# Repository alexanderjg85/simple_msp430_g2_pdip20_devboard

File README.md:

# simple_msp430_g2_pdip20_devboard

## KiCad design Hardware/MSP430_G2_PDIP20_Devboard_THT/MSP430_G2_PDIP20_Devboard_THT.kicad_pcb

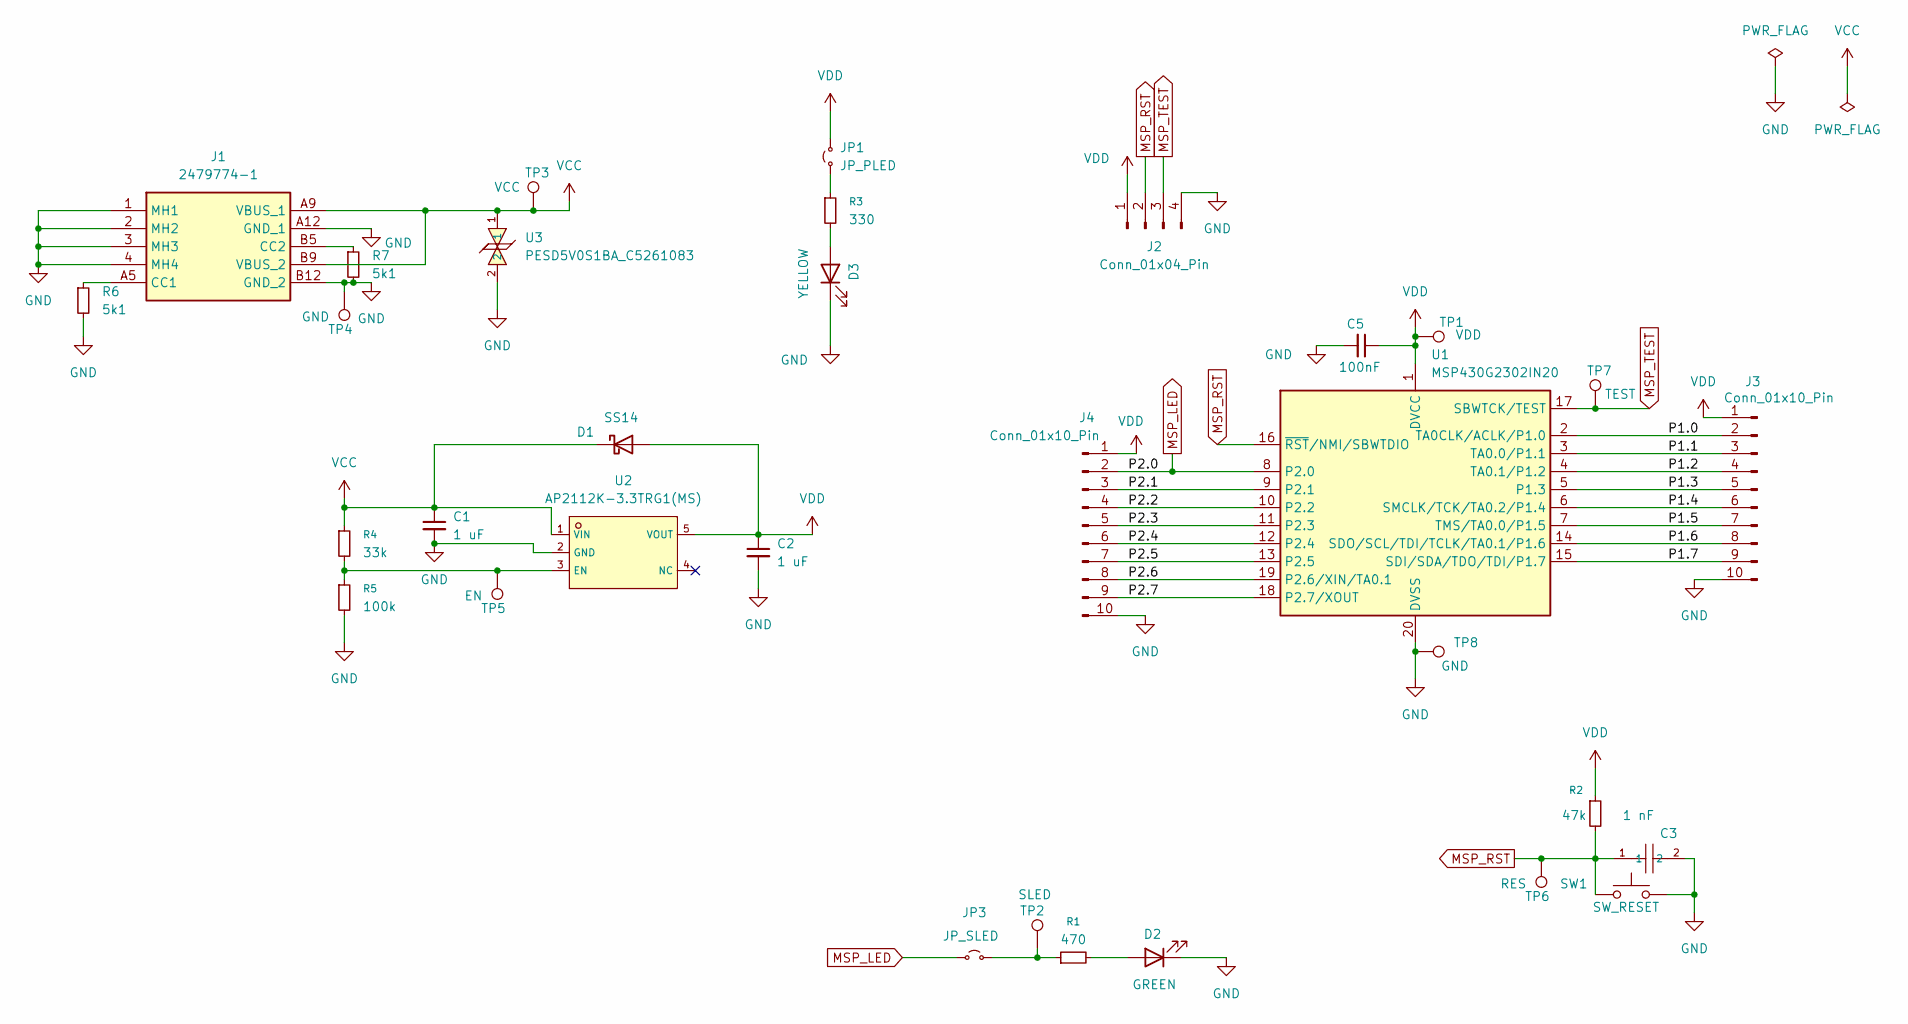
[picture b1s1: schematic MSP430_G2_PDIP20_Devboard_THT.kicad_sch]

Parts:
C1, C2: 1 uF; C6119929_C0805; LCSC C6119929
C3: 1 nF; C141155_C0805; LCSC C141155
C5: 100nF; C49678_C0805; LCSC C49678
D1: SS14; D_SMA_Handsoldering; LCSC C2480
D2: GREEN; LED_D3.0mm
D3: YELLOW; LED_D3.0mm
J1: 2479774-1; 24797741; Mouser Part Number 571-2479774-1
J2: Conn_01x04_Pin; PinHeader_1x04_P2.54mm_Vertical
J3, J4: Conn_01x10_Pin; PinHeader_1x10_P2.54mm_Vertical
JP1: JP_PLED; TestPoint_2Pads_Pitch2.54mm_Drill0.8mm
JP3: JP_SLED; TestPoint_2Pads_Pitch2.54mm_Drill0.8mm
R1: 470; R_1206_3216Metric_Pad1.30x1.75mm_HandSolder
R2: 47k; R_1206_3216Metric_Pad1.30x1.75mm_HandSolder
R3: 330; R_1206_3216Metric_Pad1.30x1.75mm_HandSolder
R4: 33k; R_0805_2012Metric_Pad1.20x1.40mm_HandSolder
R5: 100k; R_0805_2012Metric_Pad1.20x1.40mm_HandSolder; LCSC C17407
R6, R7: 5k1; C2907269_R0805; LCSC C2907269
SW1: SW_RESET; SW_SPST_PTS647_Sx38_Handsolder; MFR PN SWT0210-045026GSA
TP1: VDD; TestPoint_Pad_D1.5mm
TP2: SLED; TestPoint_Pad_D1.5mm
TP3: VCC; TestPoint_Pad_D1.5mm
TP4, TP8: GND; TestPoint_Pad_D1.5mm
TP5: EN; TestPoint_Pad_D1.5mm
TP6: RES; TestPoint_Pad_D1.5mm
TP7: TEST; TestPoint_Pad_D1.5mm
U1: MSP430G2302IN20; DIP-20_W7.62mm
U2: AP2112K-3.3TRG1(MS); C22365427_SOT-23-5_L2_9-W1_6-P0_95-LS2_7-BR; LCSC C22365427
U3: PESD5V0S1BA_C5261083; C5261083_SOD-323_L1_7-W1_3-LS2_5-BI; LCSC C5261083

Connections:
/P1.0: J3.2, U1.2 (TA0CLK/ACLK/P1.0)
/P1.1: J3.3, U1.3 (TA0.0/P1.1)
/P1.2: J3.4, U1.4 (TA0.1/P1.2)
/P1.3: J3.5, U1.5 (P1.3)
/P1.4: J3.6, U1.6 (SMCLK/TCK/TA0.2/P1.4)
/P1.5: J3.7, U1.7 (TMS/TA0.0/P1.5)
/P1.6: J3.8, U1.14 (SDO/SCL/TDI/TCLK/TA0.1/P1.6)
/P1.7: J3.9, U1.15 (SDI/SDA/TDO/TDI/P1.7)
/P2.1: J4.3, U1.9 (P2.1)
/P2.2: J4.4, U1.10 (P2.2)
/P2.3: J4.5, U1.11 (P2.3)
/P2.4: J4.6, U1.12 (P2.4)
/P2.5: J4.7, U1.13 (P2.5)
/P2.6: J4.8, U1.19 (P2.6/XIN/TA0.1)
/P2.7: J4.9, U1.18 (P2.7/XOUT)
GND: C1.2, C2.2, C3.2, C5.2, D2.1 (K), D3.1 (K), J1.1 (MH1), J1.2 (MH2), J1.3 (MH3), J1.4 (MH4), J1.A12 (GND_1), J1.B12 (GND_2), J2.4, J3.10, J4.10, R5.2, R6.2, R7.2, SW1.2, TP4.1 (1_1), TP8.1 (1_1), U1.20 (DVSS), U2.2 (GND), U3.2
MSP_LED: J4.2, JP3.1 (A), U1.8 (P2.0)
MSP_RST: C3.1, J2.2, R2.2, SW1.1, TP6.1 (1_1), U1.16 (~RST/NMI/SBWTDIO)
MSP_TEST: J2.3, TP7.1 (1_1), U1.17 (SBWTCK/TEST)
unnamed: D2.2 (A), R1.2
unnamed: D3.2 (A), R3.2
unnamed: J1.A5 (CC1), R6.1
unnamed: J1.B5 (CC2), R7.1
unnamed: JP1.1 (A), R3.1
unnamed: JP3.2 (B), R1.1, TP2.1 (1_1)
unnamed: R4.2, R5.1, TP5.1 (1_1), U2.3 (EN)
VCC: C1.1, D1.1 (K), J1.A9 (VBUS_1), J1.B9 (VBUS_2), R4.1, TP3.1 (1_1), U2.1 (VIN), U3.1
VDD: C2.1, C5.1, D1.2 (A), J2.1, J3.1, J4.1, JP1.2 (B), R2.1, TP1.1 (1_1), U1.1 (DVCC), U2.5 (VOUT)

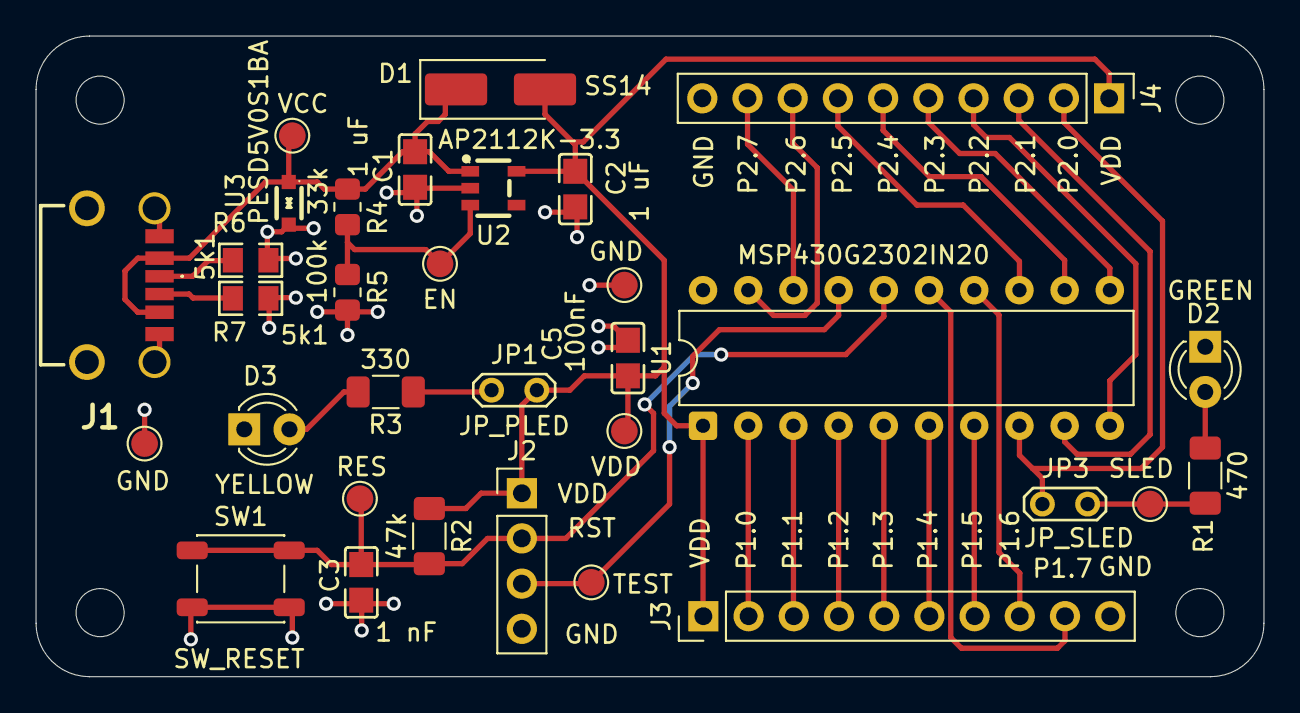
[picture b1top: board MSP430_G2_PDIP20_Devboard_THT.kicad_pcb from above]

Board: 2 copper layers, 69.0 x 36.0 mm, 32 parts (0 on the bottom side), 28 nets.

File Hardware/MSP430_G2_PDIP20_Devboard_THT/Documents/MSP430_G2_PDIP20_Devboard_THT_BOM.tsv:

Reference	Value	Spec	Qty	Package	LCSC	MFR PN
C1,C2	1 uF	 ±10% 50V	2	0805	C6119929	
C3	1 nF	 ±10% 100V	1	0805	C141155	
C5	100nF	 ±10% 50V	1	0805	C49678	
D1	SS14	30V 0.5A Schottky Diode	1	SMA	C2480	
D2	GREEN	LED GREEN	1	3 mm		
D3	YELLOW	LED YELLOW	1	3 mm		
J1	2479774-1	USB C 2.0 	1	Receptable 1x6		2479774-1
J2	Conn_01x04_Pin	Male / THT/ Vertical	1	2.54 mm 1x4		
J3,J4	Conn_01x10_Pin	Male / THT/ Vertical	2	2.54 mm 1x10		
JP1	JP_PLED	Male / THT/ Vertical	1	2.54 mm 1x2		
JP3	JP_SLED	Male / THT/ Vertical	1	2.54 mm 1x2		
R1	470	1% 125 mW	1	1206		
R2	47k	1% 125 mW	1	1206		
R3	330	1% 125 mW	1	1206		
R4	33k	1% 125 mW	1	0805		
R5	100k	1% 125 mW	1	0805	C17407	
R6,R7	5k1	1% 125 mW	2	0805	C2907269	
SW1	SW_RESET	H=4.5mm Tactile	1	4.5 x 4.5 SMD		SWT0210-045026GSA
U1	MSP430G2302	16-Bit MSP430 16 MHz	1	PDIP-20		MSP430G2302IN20
U2	AP2112K-3.3TRG1(MS)	3V3 0.6 A	1	SOT-23-5	C22365427	
U3	PESD5V0S1BA_C5261083	Vbr 5.6V Vc 8V Ipp 11A	1	SOD-323	C5261083
